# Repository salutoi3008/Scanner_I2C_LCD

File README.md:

# Scanner_I2C_LCD
Dépôt pour le projet de scanner I2C

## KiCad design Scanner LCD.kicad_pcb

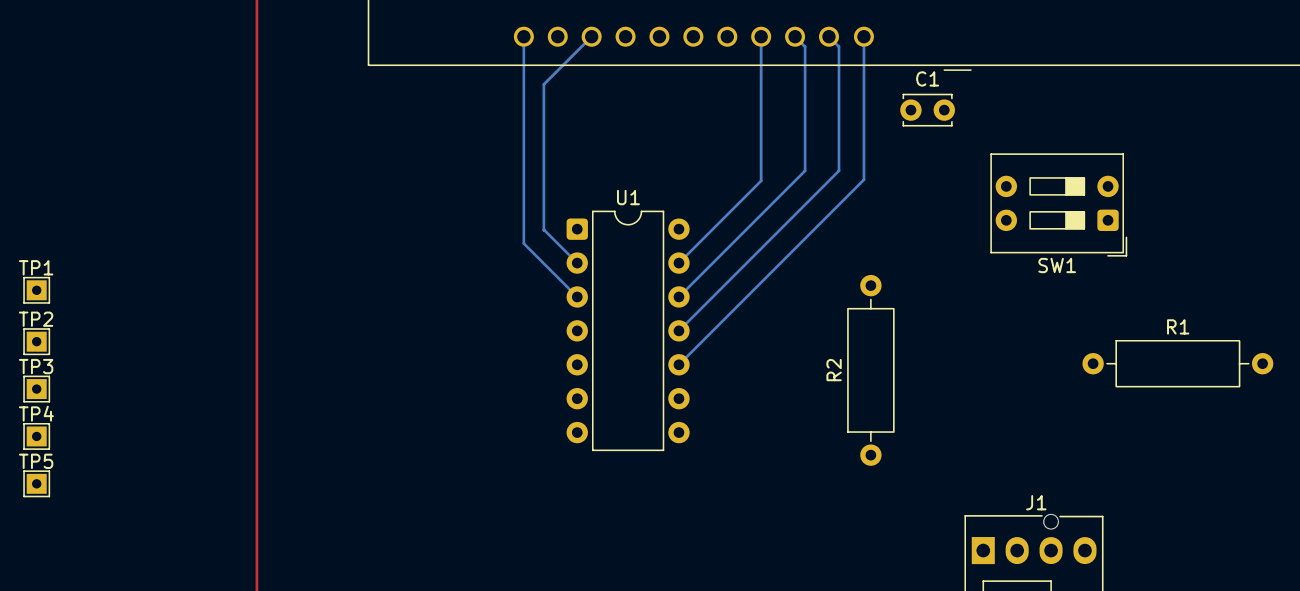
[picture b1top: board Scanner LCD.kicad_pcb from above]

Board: 2 copper layers, 12 parts (0 on the bottom side), 12 nets.

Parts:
C1: 100nF; C_Disc_D3.4mm_W2.1mm_P2.50mm
E1: LCD-016N002L
J1: Conn_01x04_Pin; FanPinHeader_1x04_P2.54mm_Vertical
R1, R2: 4700; R_Axial_DIN0309_L9.0mm_D3.2mm_P12.70mm_Horizontal
SW1: SW_DIP_x02; SW_DIP_SPSTx02_Slide_9.78x7.26mm_W7.62mm_P2.54mm
TP1, TP2, TP3, TP4, TP5: TestPoint; TestPoint_THTPad_1.5x1.5mm_Drill0.7mm
U1: ATtiny44A-P; DIP-14_W7.62mm

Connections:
+5V: C1.2, J1.4, SW1.3, SW1.4, TP4.1, U1.1 (VCC)
GND: C1.1, J1.3, U1.14 (GND)
unnamed: J1.1, R2.1, TP1.1, U1.7 (PA6)
unnamed: J1.2, R1.1, TP5.1, U1.9 (PA4)
unnamed: R1.2, SW1.1
unnamed: R2.2, SW1.2
unnamed: E1.D4, U1.13 (AREF/PA0)
unnamed: E1.D5, U1.12 (PA1)
unnamed: E1.D6, U1.11 (PA2)
unnamed: E1.D7, U1.10 (PA3)
unnamed: E1.En, TP3.1, U1.2 (XTAL1/PB0)
unnamed: E1.RS, TP2.1, U1.3 (XTAL2/PB1)
